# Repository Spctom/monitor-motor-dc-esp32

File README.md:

# Monitoramento de motor DC e controle via Wi-Fi (ESP32)

Projeto da disciplina **DPEE1107 – Sistemas Microcontrolados** (UFSM), apresentado em 25/11/2026.
Equipe: Pedro Felipe Hoffmann e Lucas Garcia Tommaselli Chuba Machado.

Bancada didática com um motor DC de 9 V e hélice, monitorado e controlado por um ESP32:

- **Medidas**: rotação (Hall 3144E), temperatura da carcaça (LM35), vibração (MPU6050) e corrente (ACS712, só como proteção).
- **Controle PI** da rotação por PWM na ponte H L298N, com feedforward, anti-windup e pulso de partida (faixa útil de ~550 a ~5200 RPM, erro ≤ 2 % acima de 1500 RPM).
- **Alarmes locais** com histerese e persistência: temperatura, corrente ou vibração altas desligam o motor; erro de rotação avisa.
- **App Android** (MIT App Inventor) e **painel web** servidos pelo próprio ESP32, inclusive na rede Wi-Fi própria `MotorDC`.
- **Thinger.io**: dashboard ao vivo e Data Bucket com as médias de cada minuto.
- Sem Wi-Fi, aquisição, controle e alarmes continuam: a rede roda numa tarefa no core 0 e o controle no core 1.

## Estrutura

| Pasta | Conteúdo |
|---|---|
| `firmware/monitor_motor/` | Sketch do Arduino IDE (core esp32 3.3.8), um módulo por sensor/função |
| `firmware/logs_ensaios/` | Logs dos ensaios automáticos (CSV), baixados com `firmware/baixar_logs.py` |
| `app/` | App do celular (`MotorDC.aia`), gerado por `gerar_aia.py` |
| `hardware/placa_conexoes/` | Placa de conexões em KiCad (não usada na montagem final, feita em placa perfurada) |
| `*.stl`, `*.SLDPRT` | Hélice e suporte do motor |
| `APRESENTACAO.md` | Roteiro da apresentação |
| `CLAUDE.md` | Notas técnicas completas: ligações, decisões, resultados dos ensaios e problemas encontrados |

## Como compilar

1. Copie `firmware/monitor_motor/secrets.example.h` para `secrets.h` e preencha as redes Wi-Fi e as credenciais do Thinger.io (sem o arquivo, o firmware roda só com as funções locais).
2. Instale a biblioteca `thinger.io` (2.49.0) e compile para a placa "ESP32 Dev Module".

## Limitações conhecidas

- O ACS712 não tem resolução para a corrente deste motor (~100–170 mA): serve só como proteção contra sobrecorrente.
- Buzzer e display LCD ficaram de fora por defeito nos componentes: o alarme local é visual (LEDs).
- Algumas redes bloqueiam a conexão TLS do Thinger.io (porta 25202); na apresentação foi usado o hotspot do celular.

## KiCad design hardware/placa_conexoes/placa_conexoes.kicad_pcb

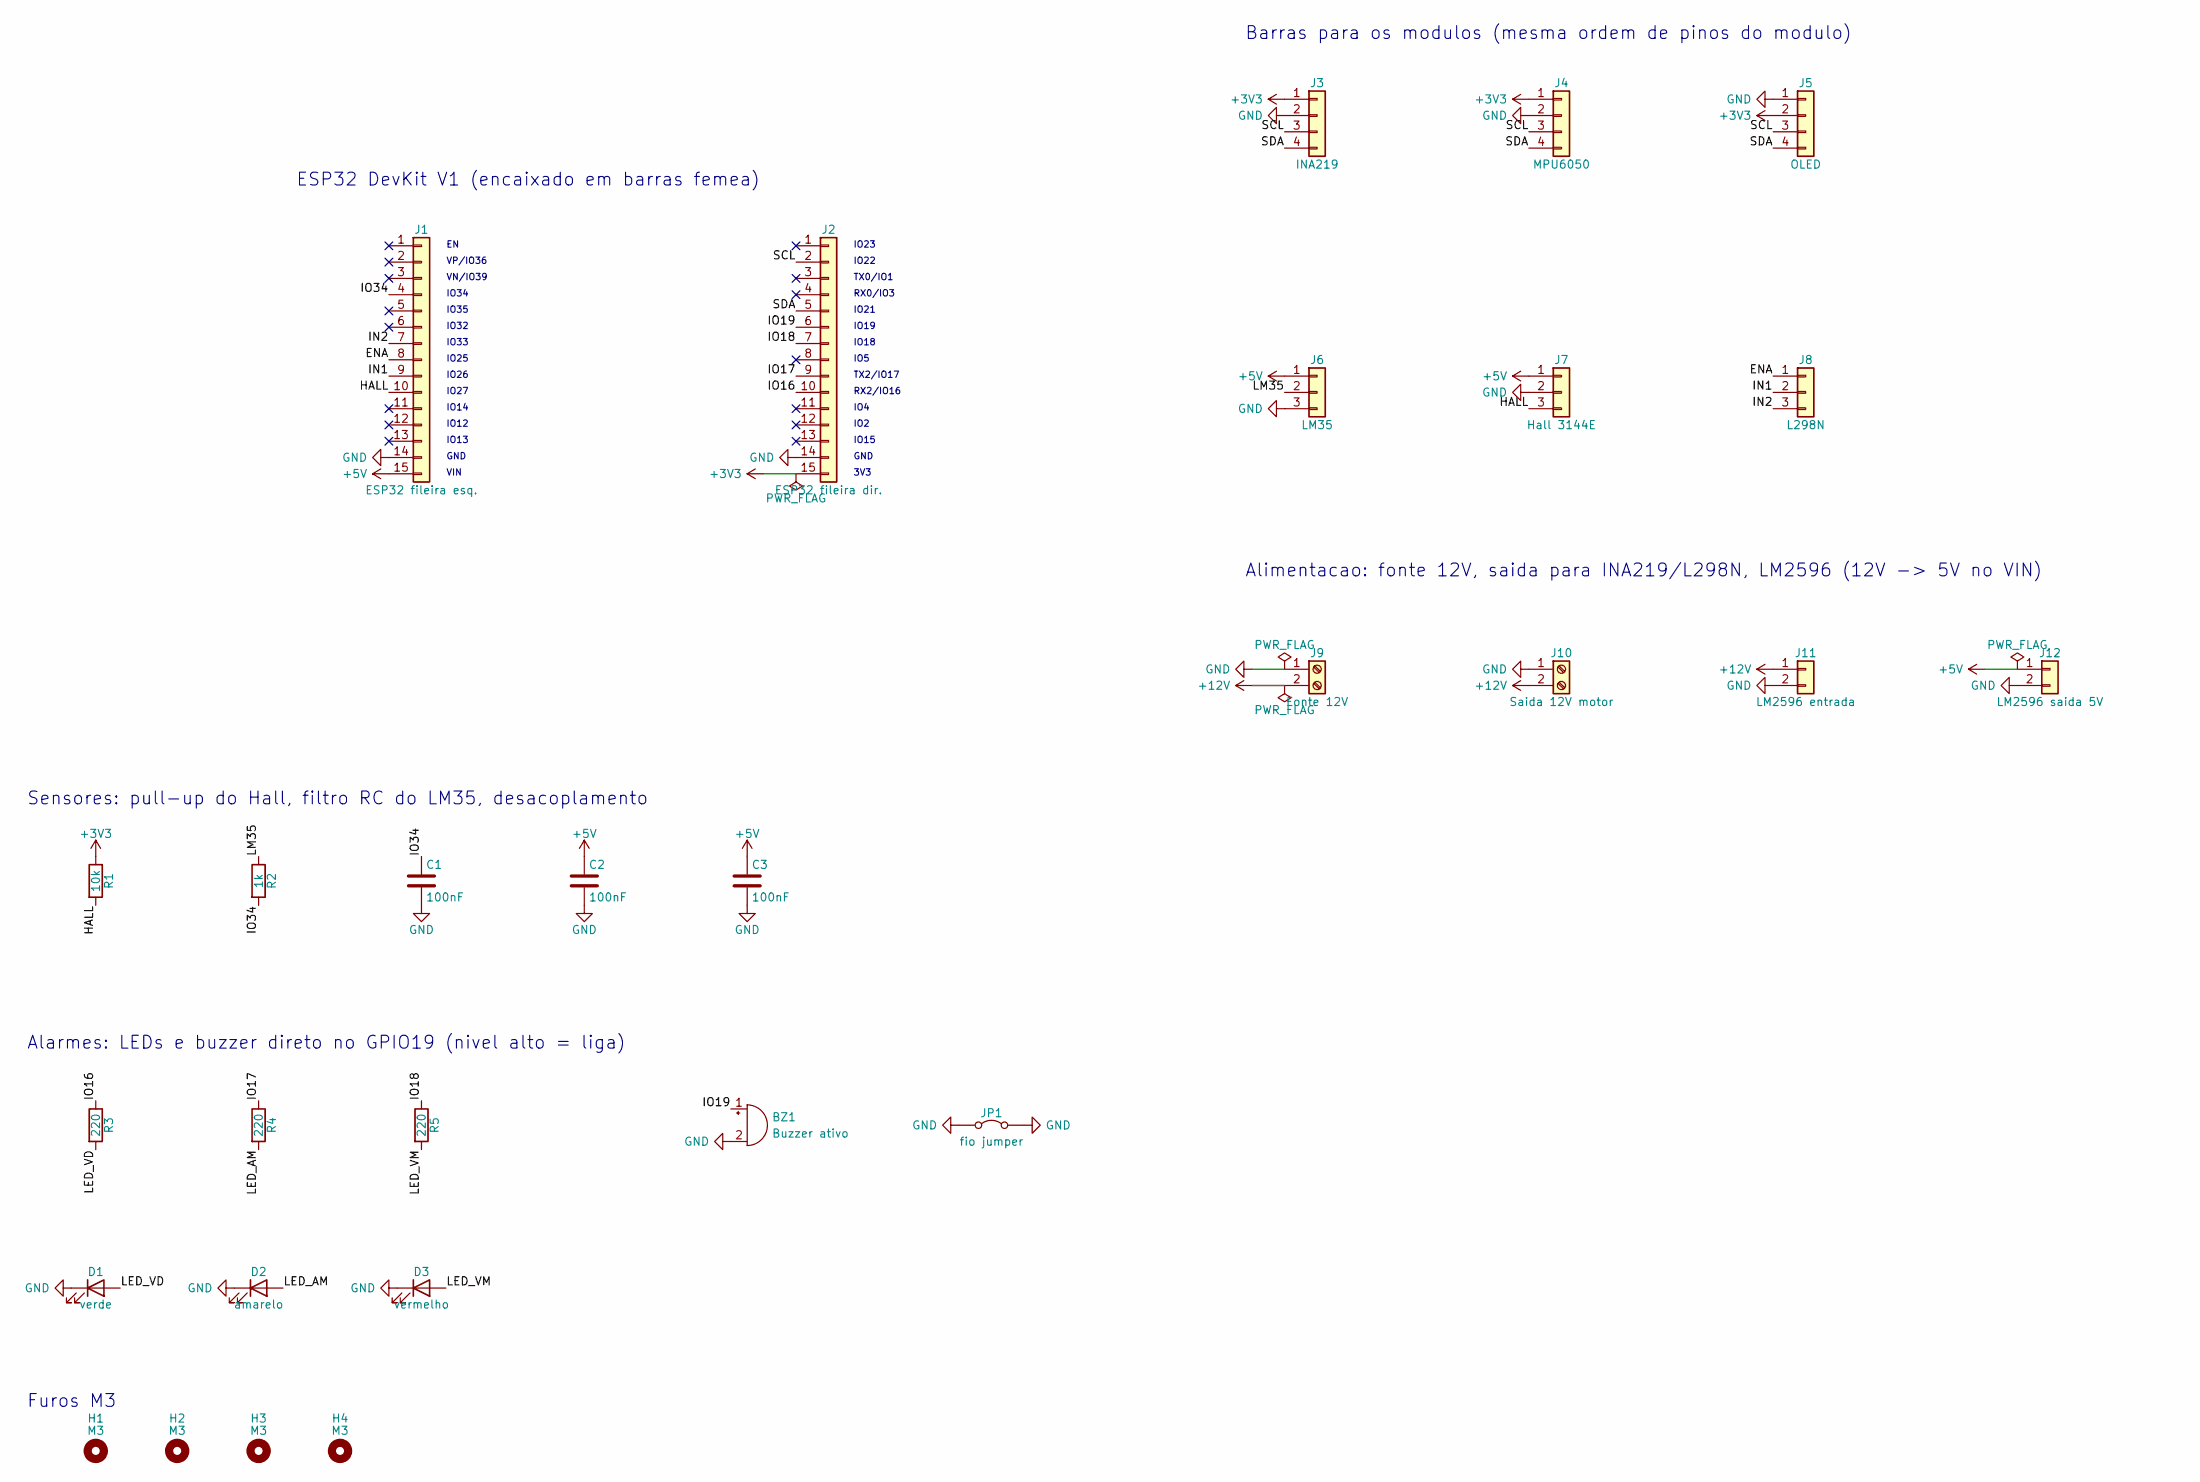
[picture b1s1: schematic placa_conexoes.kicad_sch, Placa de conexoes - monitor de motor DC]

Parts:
BZ1: Buzzer ativo; Buzzer_12x9.5RM7.6
C1, C2, C3: 100nF; C_Disc_D5.0mm_W2.5mm_P5.00mm
D1: verde; LED_D5.0mm
D2: amarelo; LED_D5.0mm
D3: vermelho; LED_D5.0mm
H1, H2, H3, H4: M3; MountingHole_3.2mm_M3
J1: ESP32 fileira esq.; PinSocket_1x15_P2.54mm_Vertical
J2: ESP32 fileira dir.; PinSocket_1x15_P2.54mm_Vertical
J3: INA219; PinSocket_1x04_P2.54mm_Vertical
J4: MPU6050; PinSocket_1x04_P2.54mm_Vertical
J5: OLED; PinSocket_1x04_P2.54mm_Vertical
J6: LM35; PinSocket_1x03_P2.54mm_Vertical
J7: Hall 3144E; PinSocket_1x03_P2.54mm_Vertical
J8: L298N; PinSocket_1x03_P2.54mm_Vertical
J9: Fonte 12V; TerminalBlock_Phoenix_MKDS-1,5-2-5.08_1x02_P5.08mm_Horizont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
J10: Saida 12V motor; TerminalBlock_Phoenix_MKDS-1,5-2-5.08_1x02_P5.08mm_Horizont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
J11: LM2596 entrada; PinHeader_1x02_P2.54mm_Vertical
J12: LM2596 saida 5V; PinHeader_1x02_P2.54mm_Vertical
JP1: fio jumper; R_Axial_DIN0207_L6.3mm_D2.5mm_P7.62mm_Horizontal
R1: 10k; R_Axial_DIN0207_L6.3mm_D2.5mm_P7.62mm_Horizontal
R2: 1k; R_Axial_DIN0207_L6.3mm_D2.5mm_P7.62mm_Horizontal
R3, R4, R5: 220; R_Axial_DIN0207_L6.3mm_D2.5mm_P7.62mm_Horizontal

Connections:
+3V3: J2.15, J3.1, J4.1, J5.2, R1.1
+5V: C2.1, C3.1, J1.15, J6.1, J7.1, J12.1
+12V: J9.2, J10.2, J11.1
/ENA: J1.8, J8.1
/HALL: J1.10, J7.3, R1.2
/IN1: J1.9, J8.2
/IN2: J1.7, J8.3
/IO16: J2.10, R3.1
/IO17: J2.9, R4.1
/IO18: J2.7, R5.1
/IO19: BZ1.1 (+), J2.6
/IO34: C1.1, J1.4, R2.2
/LED_AM: D2.2 (A), R4.2
/LED_VD: D1.2 (A), R3.2
/LED_VM: D3.2 (A), R5.2
/LM35: J6.2, R2.1
/SCL: J2.2, J3.3, J4.3, J5.3
/SDA: J2.5, J3.4, J4.4, J5.4
GND: BZ1.2 (-), C1.2, C2.2, C3.2, D1.1 (K), D2.1 (K), D3.1 (K), J1.14, J2.14, J3.2, J4.2, J5.1, J6.3, J7.2, J9.1, J10.1, J11.2, J12.2, JP1.1 (A), JP1.2 (B)

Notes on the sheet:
VP/IO36
VN/IO39
IO34
IO35
IO32
IO33
IO25
IO26
IO27
IO14
IO12
IO13
GND
VIN
IO23
IO22
TX0/IO1
RX0/IO3
IO21
IO19
IO18
IO5
TX2/IO17
RX2/IO16
IO4
IO2
IO15
3V3
ESP32 DevKit V1 (encaixado em barras femea)
Barras para os modulos (mesma ordem de pinos do modulo)
Alimentacao: fonte 12V, saida para INA219/L298N, LM2596 (12V -> 5V no VIN)
Sensores: pull-up do Hall, filtro RC do LM35, desacoplamento
Alarmes: LEDs e buzzer direto no GPIO19 (nivel alto = liga)
Furos M3

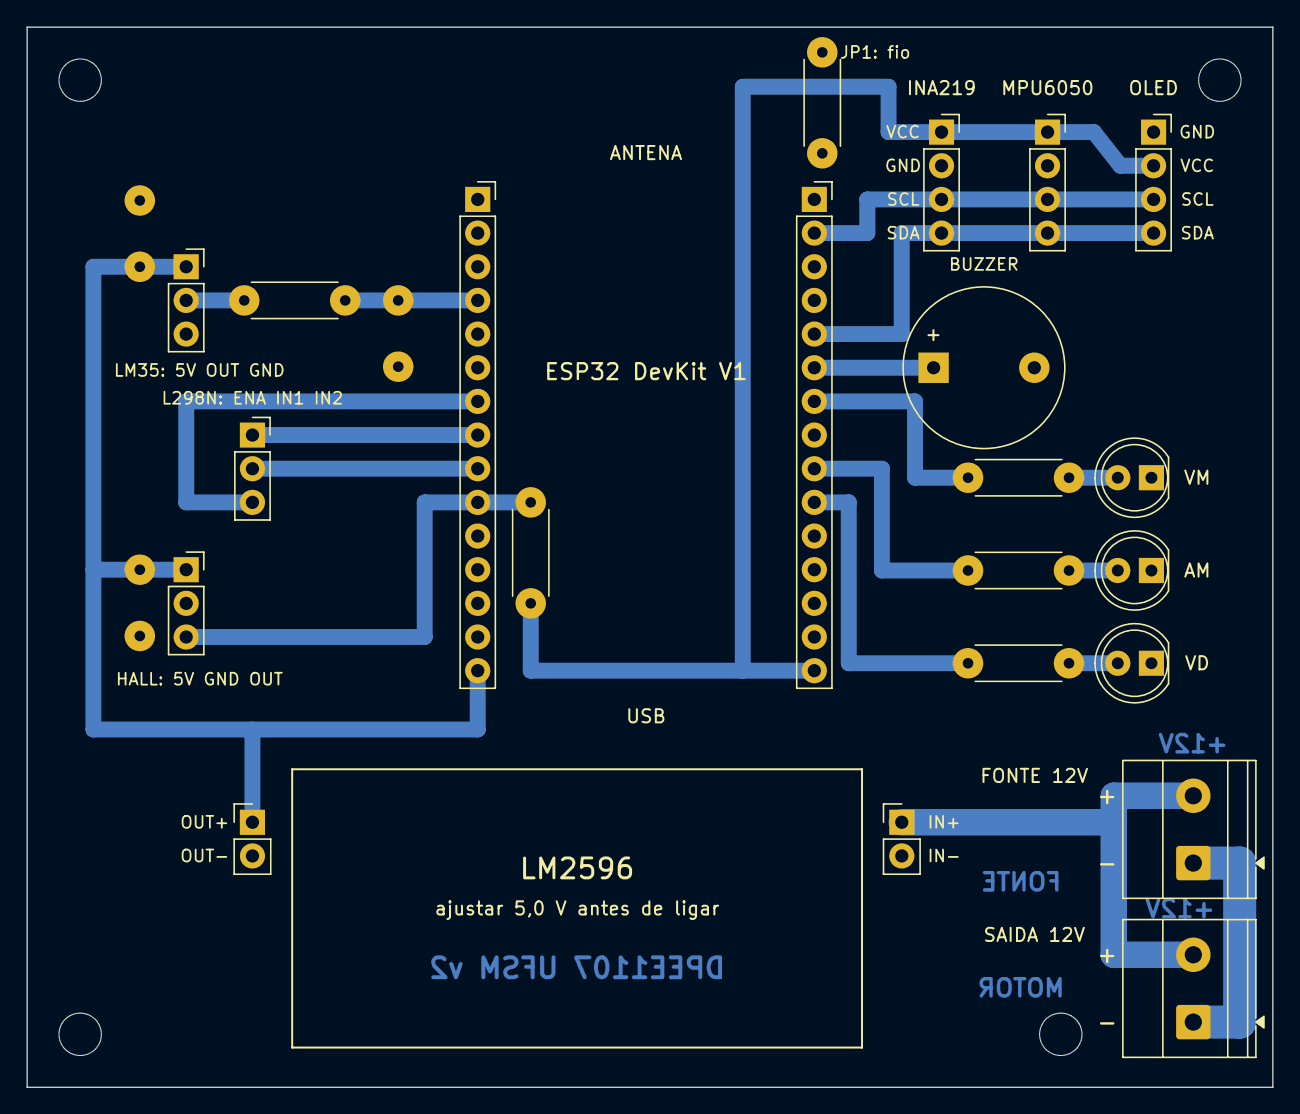
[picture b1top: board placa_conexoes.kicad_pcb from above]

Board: 2 copper layers, 94.0 x 80.0 mm, 29 parts (0 on the bottom side), 19 nets.

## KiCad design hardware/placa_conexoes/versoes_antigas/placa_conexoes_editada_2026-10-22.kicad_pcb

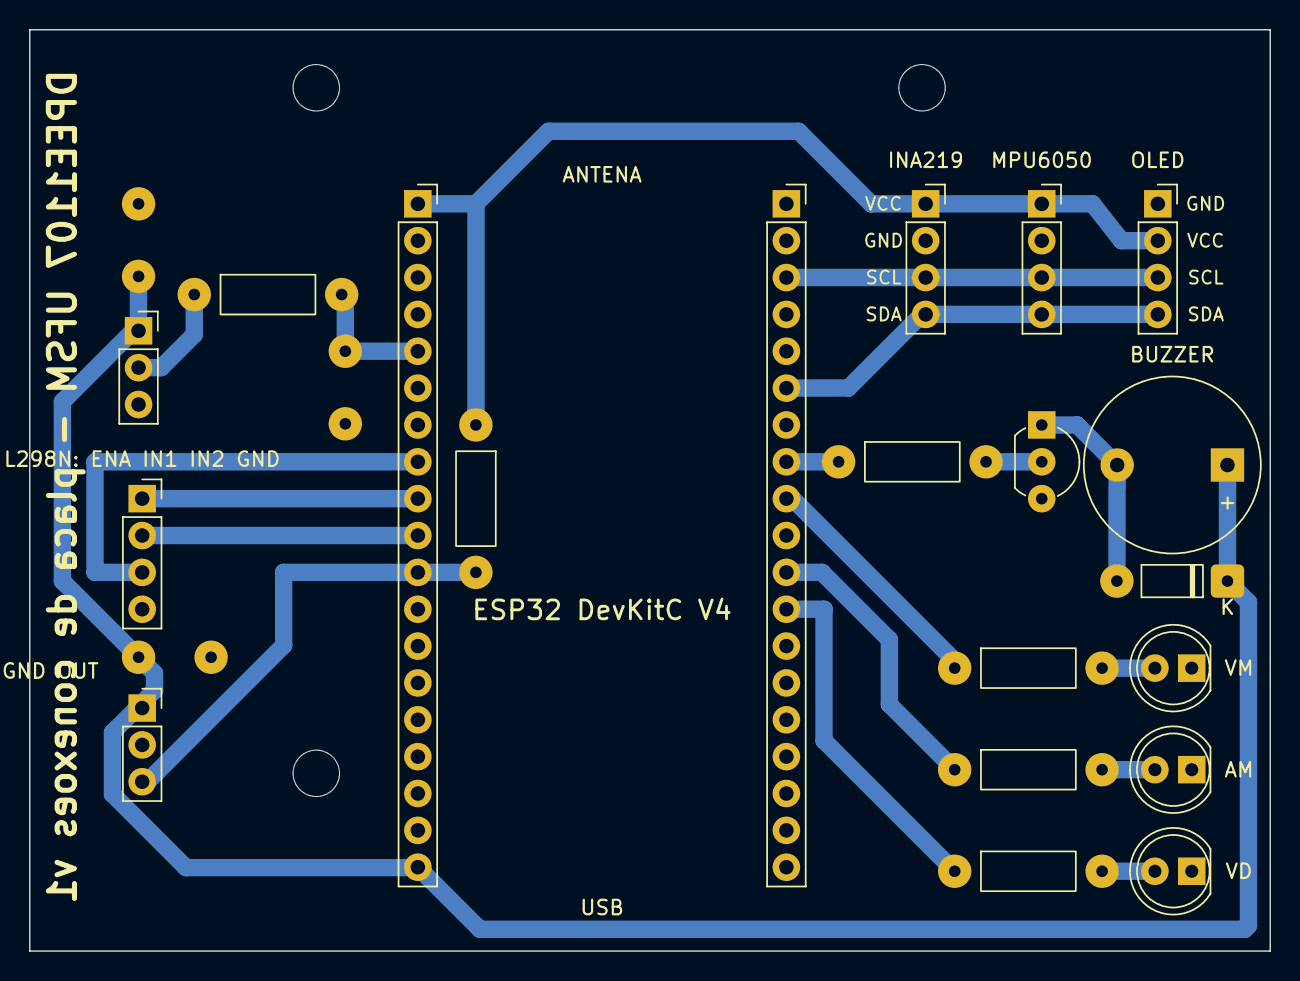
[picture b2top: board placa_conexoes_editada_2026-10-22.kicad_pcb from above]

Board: 2 copper layers, 85.5 x 63.5 mm, 26 parts (0 on the bottom side), 20 nets.

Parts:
BZ1: Buzzer 5V; Buzzer_12x9.5RM7.6
C1, C2, C3: 100nF; C_Disc_D5.0mm_W2.5mm_P5.00mm
D1: verde; LED_D5.0mm
D2: amarelo; LED_D5.0mm
D3: vermelho; LED_D5.0mm
D4: 1N4148; D_DO-35_SOD27_P7.62mm_Horizontal
H1, H2, H3: M3; MountingHole_3.2mm_M3
J1: ESP32 fileira esq.; PinSocket_1x19_P2.54mm_Vertical
J2: ESP32 fileira dir.; PinSocket_1x19_P2.54mm_Vertical
J3: INA219; PinSocket_1x04_P2.54mm_Vertical
J4: MPU6050; PinSocket_1x04_P2.54mm_Vertical
J5: OLED; PinSocket_1x04_P2.54mm_Vertical
J6: LM35; PinSocket_1x03_P2.54mm_Vertical
J7: Hall 3144E; PinSocket_1x03_P2.54mm_Vertical
J8: L298N; PinSocket_1x04_P2.54mm_Vertical
Q1: BC547; TO-92_Inline_Wide
R1: 10k; R_Axial_DIN0207_L6.3mm_D2.5mm_P10.16mm_Horizontal
R2, R6: 1k; R_Axial_DIN0207_L6.3mm_D2.5mm_P10.16mm_Horizontal
R3, R4, R5: 220; R_Axial_DIN0207_L6.3mm_D2.5mm_P10.16mm_Horizontal

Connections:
+3V3: J1.1, J3.1, J4.1, J5.2, R1.1
+5V: BZ1.1, C2.1, C3.1, D4.1, J1.19, J6.1, J7.1
/BASE_Q1: Q1.2, R6.2
/BUZ-: BZ1.2, D4.2, Q1.1
/ENA: J1.9, J8.1
/HALL: J1.11, J7.3, R1.2
/IN1: J1.10, J8.2
/IN2: J1.8, J8.3
/IO16: J2.12, R3.1
/IO17: J2.11, R4.1
/IO18: J2.9, R5.1
/IO19: J2.8, R6.1
/IO34: C1.1, J1.5, R2.2
/LED_AM: D2.2, R4.2
/LED_VD: D1.2, R3.2
/LED_VM: D3.2, R5.2
/LM35: J6.2, R2.1
/SCL: J2.3, J3.3, J4.3, J5.3
/SDA: J2.6, J3.4, J4.4, J5.4
GND: C1.2, C2.2, C3.2, D1.1, D2.1, D3.1, J1.14, J2.1, J2.7, J3.2, J4.2, J5.1, J6.3, J7.2, J8.4, Q1.3
